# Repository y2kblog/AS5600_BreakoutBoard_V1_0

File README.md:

# 12bit (4096P/R) 磁気式エンコーダAS5600 Breakout Board

[English page](https://products.y2kb.com/en/as5600/latest/)

## 概要

12bit (4096P/R) 分解能の磁気式アブソリュートエンコーダ AS5600 (ams AG製) を2.54mmピッチに変換する基板です。ネオジム磁石を同梱。  
5V、3.3V、GNDの電源ピンとI2C、アナログ/PWM出力のピンが出ています。電源電圧は5Vもしくは3.3Vです。  
**※AS5601との違いはAS5601の出力方式がA/B相のインクリメンタル出力であるのに対し、AS5600はアナログ/PWM出力である点です。**  

※本ボードは[DCモータ制御シールドV1.0](https://github.com/y2kblog/DCMotorControlShieldV1_0)にも使用しています。

### AS5600の特徴
- 4096P/R の高分解能
- 磁気式のため非接触で角度計測が可能であり、信頼性と耐久性に優れている
- インターフェイス：I2C、アナログ出力もしくはPWM出力
- アナログ出力：角度に対応したアナログ電圧値を出力
- PWM出力：角度に対応したデューティ比のPWM信号を出力
- I2C：設定レジスタにアクセスでき、角度の読み取りや動作設定が可能
- サンプリング時間：150μs
- AS5600とネオジム磁石の中心が1mm程度ずれても値の読み取りが可能

### 基板仕様
- 基板サイズ：横20mm×縦13.5ｍｍ
- 基板マウント用穴：15mmピッチ、M3×2穴
- 電源電圧に5Vを供給する場合は3.3Vピンをオープンに、3.3Vを供給する場合は5Vピンにも3.3Vを供給してください。
- DIRピンはGNDに接続、PGOピンは非接続

## 販売  
[スイッチサイエンス委託販売ページ](https://www.switch-science.com/catalog/3493/)  
※大量注文や在庫に関する問い合わせは[こちら](mailto:info.y2kb@gmail.com)までご連絡ください。  

## 内容物
- AS5600 Breakout Board 本体
- エンコーダ用ネオジム磁石

### 回路図  

### 寸法  

## 取付方法
1. 同梱のネオジム磁石を回転体の軸中心に取り付けます
2. AS5600の中心とネオジム磁石の中心が合うよう基板を固定部に取り付けます

**取付例**  

## Arduinoによるプログラム例  

### I2Cによる角度の取得  
#### 配線図  

#### [ソースファイル](https://github.com/y2kblog/AS5600_BreakoutBoard_V1_0/blob/master/SampleCode/Arduino/I2C_SampleCode/I2C_SampleCode.ino)

<!--
#### ソースファイルのディレクトリ  
"SampleCode/Arduino/I2C_SampleCode/I2C_SampleCode.ino"
-->

#### ミニマムコード  

```cpp
#include <stdint.h>
#include <Wire.h>
#define AS5600_AS5601_DEV_ADDRESS      0x36
#define AS5600_AS5601_REG_RAW_ANGLE    0x0C

void setup() {
  // I2C init
  Wire.begin();
  Wire.setClock(400000);

  // Read RAW_ANGLE value from encoder
  Wire.beginTransmission(AS5600_AS5601_DEV_ADDRESS);
  Wire.write(AS5600_AS5601_REG_RAW_ANGLE);
  Wire.endTransmission(false);
  Wire.requestFrom(AS5600_AS5601_DEV_ADDRESS, 2);
  uint16_t RawAngle = 0;
  RawAngle  = ((uint16_t)Wire.read() << 8) & 0x0F00;
  RawAngle |= (uint16_t)Wire.read();
  // Raw angle value (0 ~ 4095) is stored in RawAngle
}

void loop() {
}
```

### アナログピンを用いた角度の取得  
#### 配線図  

#### [ソースファイル](https://github.com/y2kblog/AS5600_BreakoutBoard_V1_0/blob/master/SampleCode/Arduino/Analog_SampleCode/Analog_SampleCode.ino)

<!--
#### ソースファイルのディレクトリ  
"SampleCode/Arduino/I2C_SampleCode/Analog_SampleCode.ino"
-->

#### ミニマムコード  

```cpp
#include <stdint.h>

void setup() {
  uint16_t AnalogValue = 0;
  AnalogValue = analogRead(0);
  AnalogValue &= 0x03FF;
  AnalogValue = 0x03FF - AnalogValue;
  // Angle value (0 ~ 1023) is stored in AnalogValue
}

void loop() {
}
```

<!--
#### STM32 (HAL)

**サンプルコード**
```c
// I2Cの初期化は終わっているとする

#define AS5600_AS5601_DEV_ADDRESS      (0x36<<1)
#define AS5600_AS5601_REG_RAW_ANGLE    0x0C

uint8_t buf[2];
HAL_I2C_Mem_Read(&hi2c, AS5600_AS5601_DEV_ADDRESS,
  AS5600_AS5601_REG_RAW_ANGLE, I2C_MEMADD_SIZE_8BIT,
  (uint8_t*)buf, 2, 1000);
uint16_t RawAngle;
RawAngle = (uint16_t) buf[0] << 8 | (uint16_t) buf[1];
RawAngle &= 0x0FFF;
// Raw angle value (0x0000~0x0FFF) is stored in RawAngle
```
-->

## 資料

- 2Dデータ(DXF)：<a href="https://github.com/y2kblog/AS5600_BreakoutBoard_V1_0/raw/master/PCB_source/dxf/AS5600_BreakoutBoard_V1_0_dxf.zip" download="">AS5600_BreakoutBoard_V1_0_dxf.zip</a>  
- 3Dデータ(STEP)：<a href="https://github.com/y2kblog/AS5600_BreakoutBoard_V1_0/raw/master/PCB_source/step/AS5600_BreakoutBoard_V1_0_step.zip" download="">AS5600_BreakoutBoard_V1_0_step.zip</a>  

## License
MIT License

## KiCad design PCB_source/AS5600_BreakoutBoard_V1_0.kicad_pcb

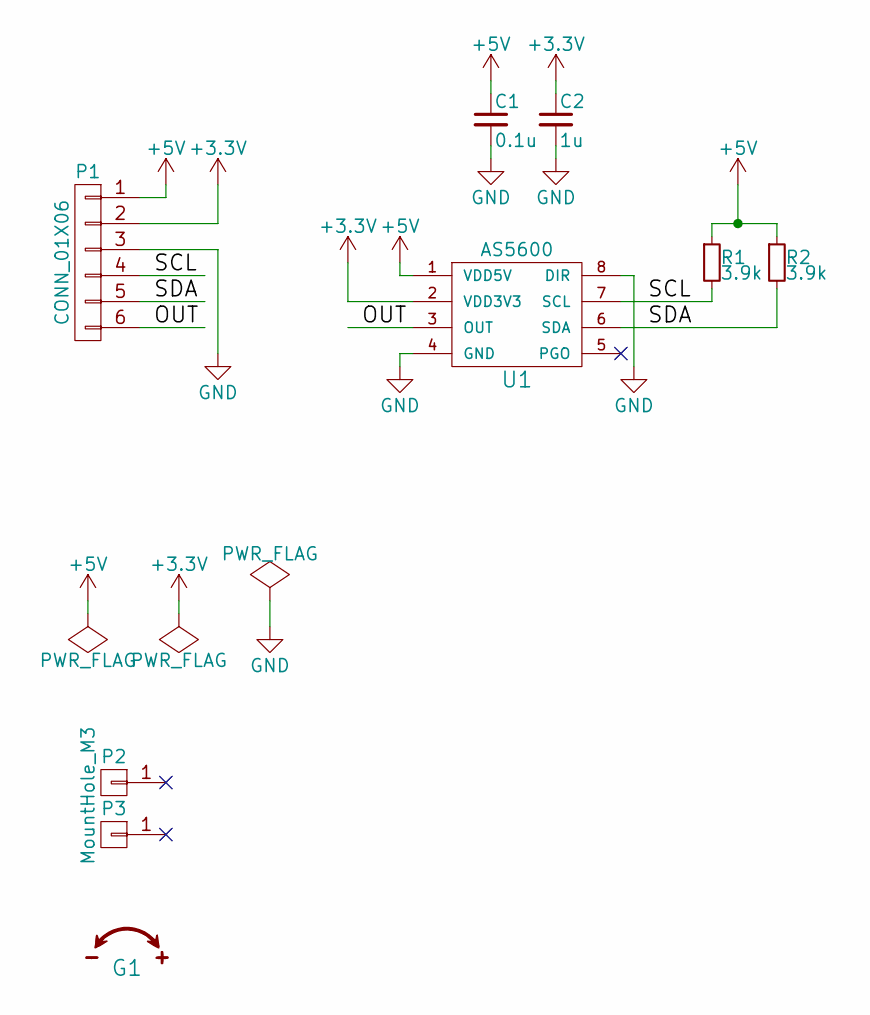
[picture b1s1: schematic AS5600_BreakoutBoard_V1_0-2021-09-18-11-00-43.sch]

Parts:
C1: 0.1u; C_0603_HandSoldering
C2: 1u; C_0603_HandSoldering
G1: LOGO; Logo_DirRot_v01
P1: CONN_01X06; USER_SIL-6
P2, P3: MountHole_M3; MountingHole_3.2mm_M3
R1, R2: 3.9k; R_0603_HandSoldering
U1: AS5600; SOIC-8_3.9x4.9mm_Pitch1.27mm

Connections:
+3V3: C2.1, P1.2, U1.2 (VDD3V3)
+5V: C1.1, P1.1, R1.1, R2.1, U1.1 (VDD5V)
/OUT: P1.6, U1.3 (OUT)
/SCL: P1.4, R1.2, U1.7 (SCL)
/SDA: P1.5, R2.2, U1.6 (SDA)
GND: C1.2, C2.2, P1.3, U1.4 (GND), U1.8 (DIR)

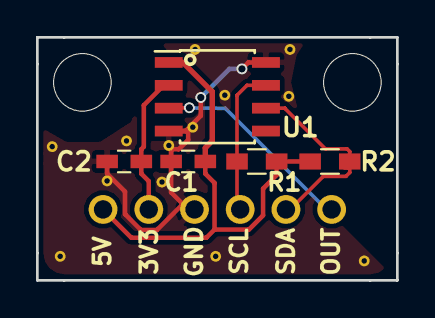
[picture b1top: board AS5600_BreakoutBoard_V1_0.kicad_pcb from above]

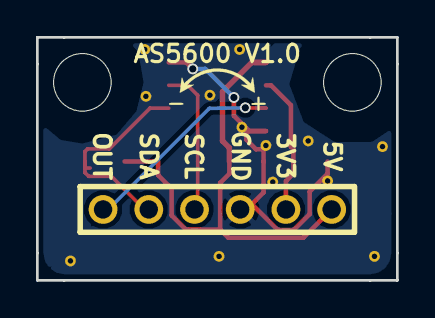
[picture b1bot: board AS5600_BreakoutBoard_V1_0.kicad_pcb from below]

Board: 2 copper layers, 20.0 x 13.5 mm, 9 parts (2 on the bottom side), 6 nets.

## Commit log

2017-09-03 :space_invader: Added .gitattributes & .gitignore files
2017-09-03 init
2017-09-03 fix README
2017-09-07 fix sample code bug
2017-09-17 Add sample code using Analog output
2017-09-22 Add circuit diagram
2021-09-18 add step and refactoring
2021-09-18 syntax highlighting
2021-09-23 add DXF
